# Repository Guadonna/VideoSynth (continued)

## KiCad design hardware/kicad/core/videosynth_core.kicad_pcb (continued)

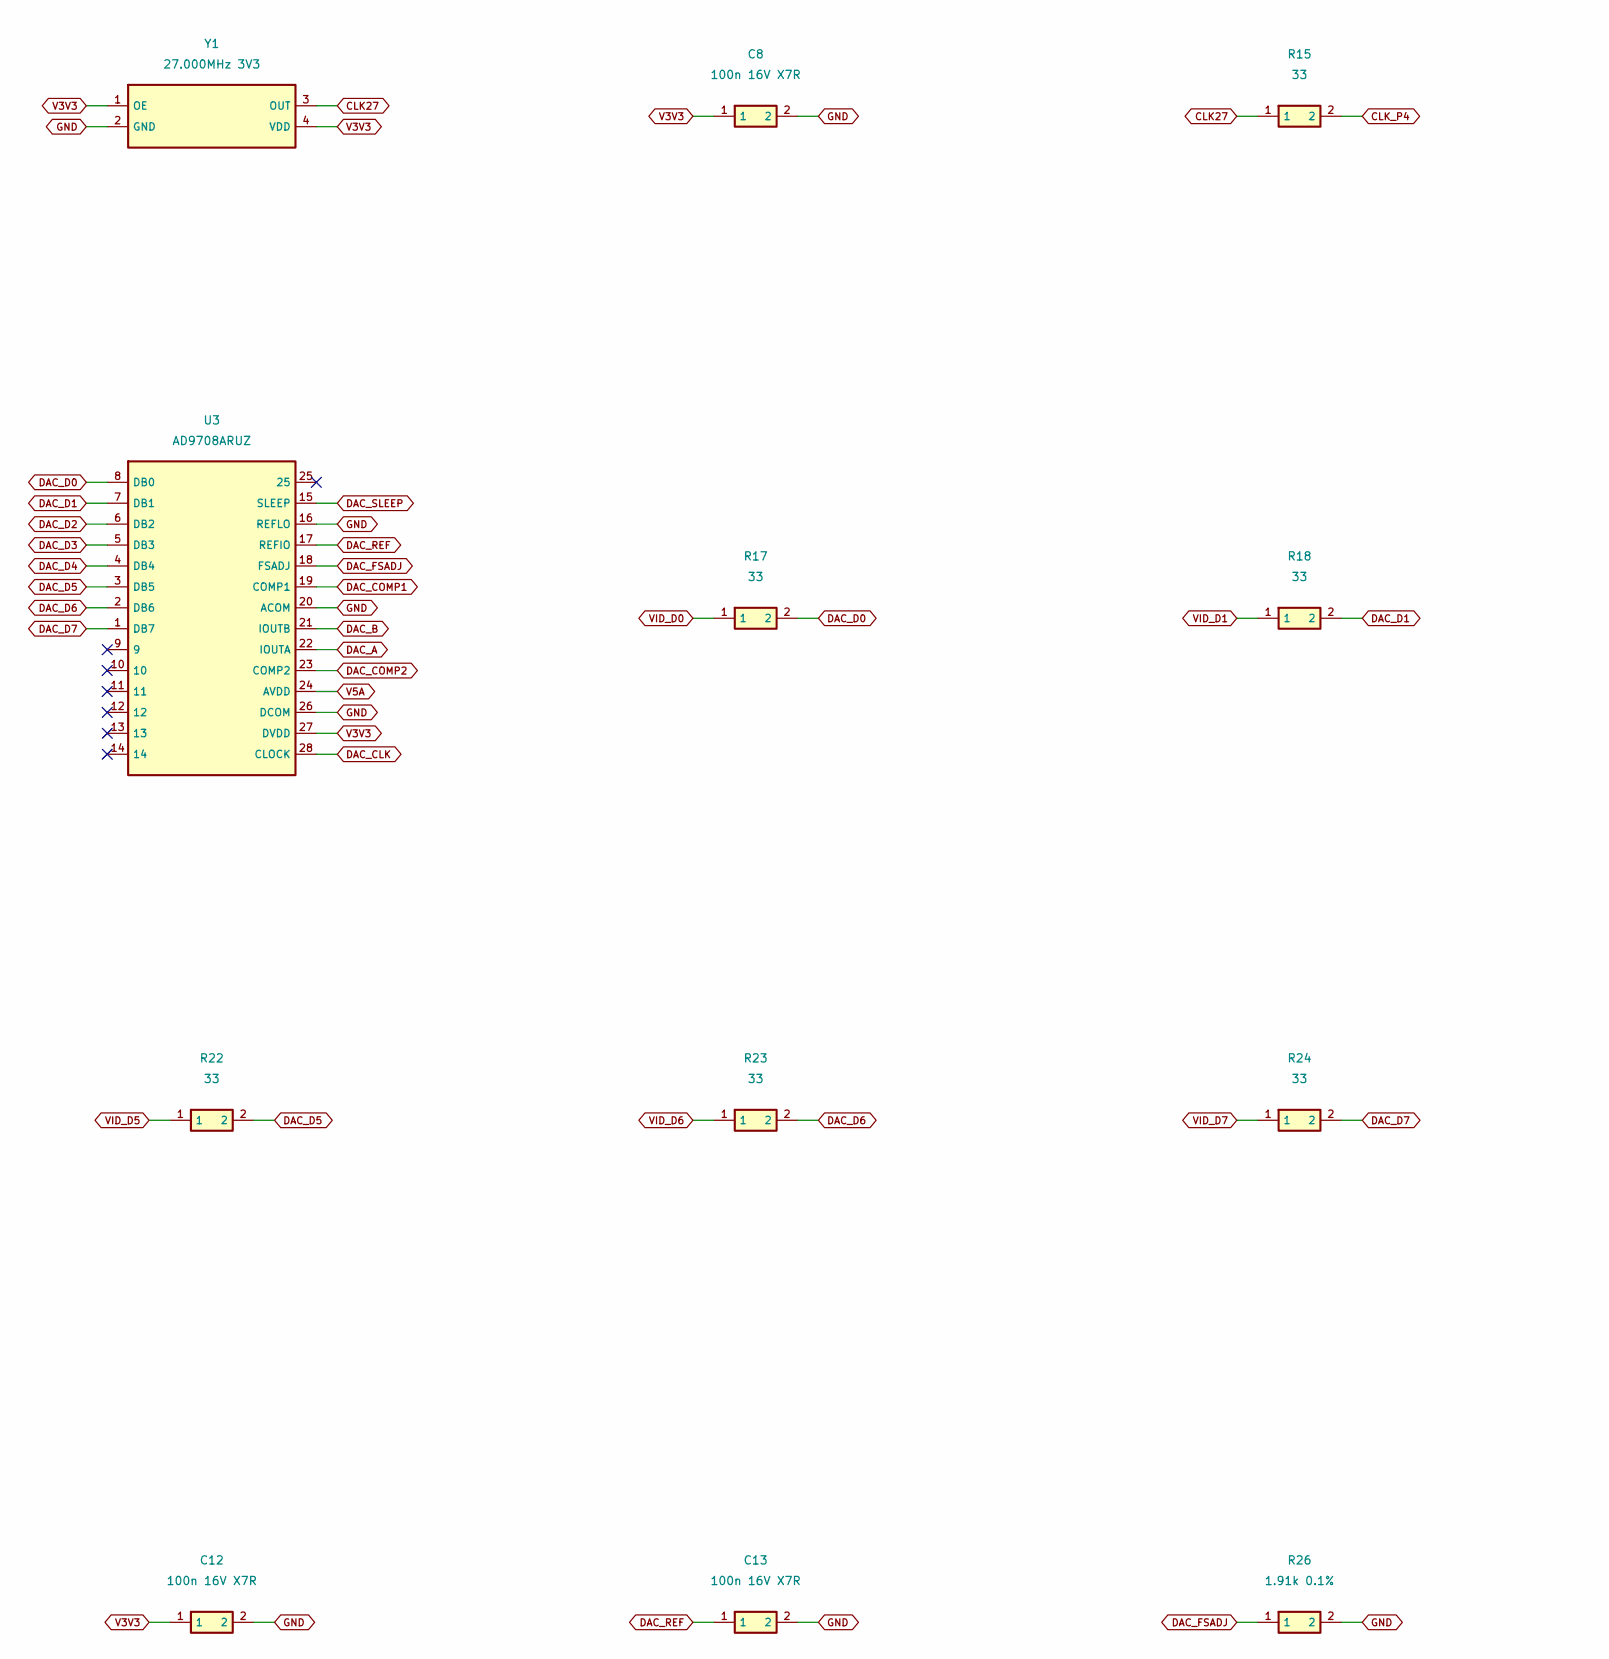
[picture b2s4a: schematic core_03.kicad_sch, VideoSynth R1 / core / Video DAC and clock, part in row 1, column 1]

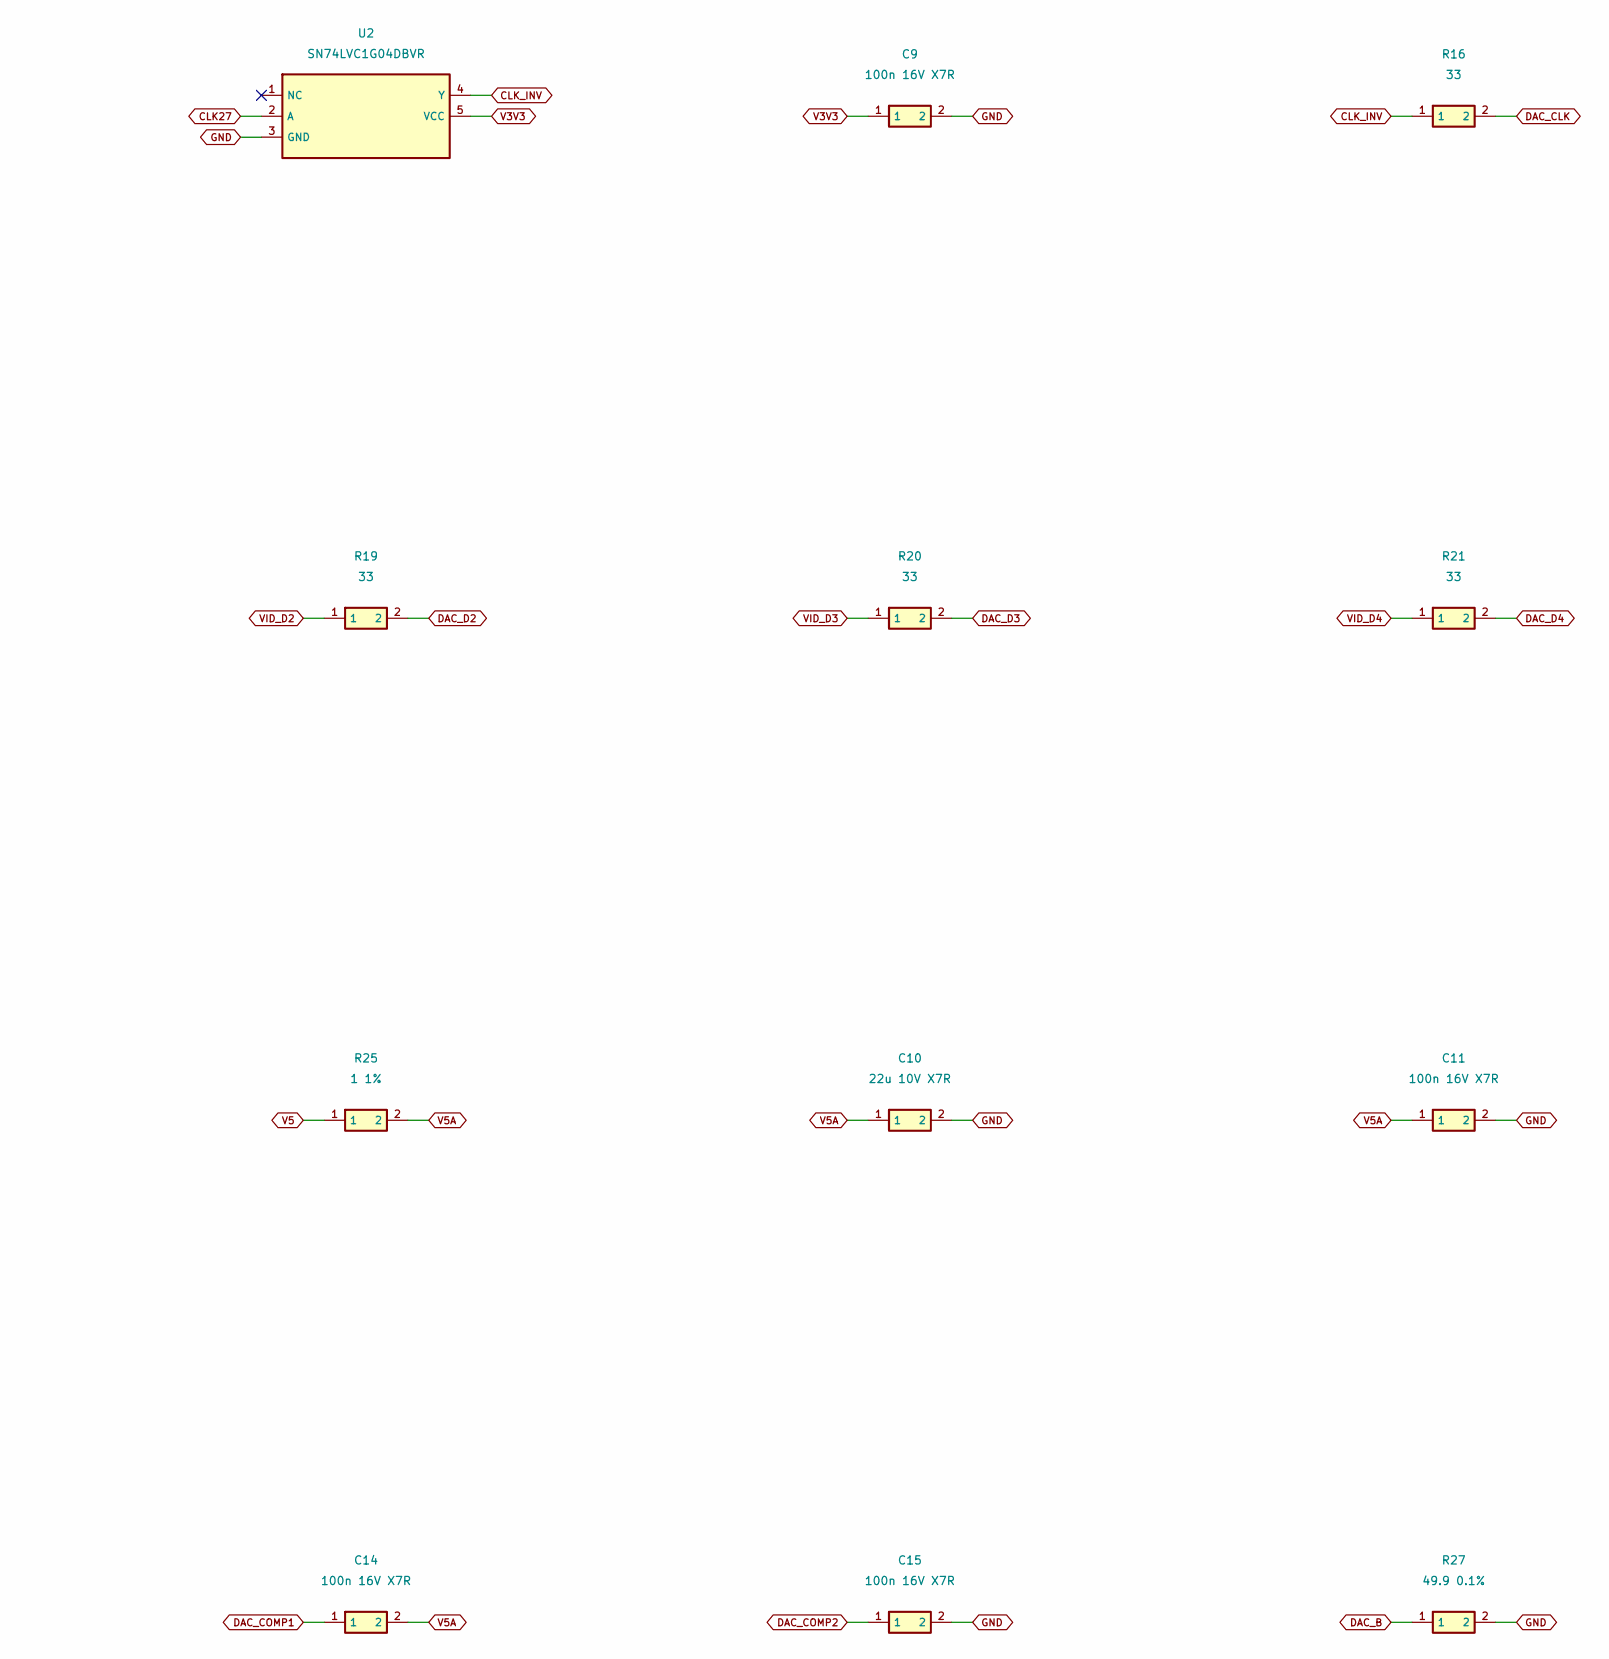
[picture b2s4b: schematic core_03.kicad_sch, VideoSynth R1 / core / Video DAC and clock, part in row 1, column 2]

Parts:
C8, C9, C11, C12, C13, C14, C15: 100n 16V X7R; C_0805_2012Metric
C10: 22u 10V X7R; C_0805_2012Metric
R15, R16, R17, R18, R19, R20, R21, R22, R23, R24: 33; R_0805_2012Metric
R25: 1 1%; R_0805_2012Metric
R26: 1.91k 0.1%; R_0805_2012Metric
R27: 49.9 0.1%; R_0805_2012Metric
U2: SN74LVC1G04DBVR; SOT-23-5
U3: AD9708ARUZ; TSSOP-28_4.4x9.7mm_P0.65mm
Y1: 27.000MHz 3V3; Oscillator_SMD_Abracon_ASE-4Pin_3.2x2.5mm

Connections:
CLK27: R15.1, U2.2 (A), Y1.3 (OUT)
CLK_INV: R16.1, U2.4 (Y)
CLK_P4: R15.2; also elsewhere on the board
DAC_A: U3.22 (IOUTA); also elsewhere on the board
DAC_B: R27.1, U3.21 (IOUTB)
DAC_CLK: R16.2, U3.28 (CLOCK)
DAC_COMP1: C14.1, U3.19 (COMP1)
DAC_COMP2: C15.1, U3.23 (COMP2)
DAC_D0: R17.2, U3.8 (DB0)
DAC_D1: R18.2, U3.7 (DB1)
DAC_D2: R19.2, U3.6 (DB2)
DAC_D3: R20.2, U3.5 (DB3)
DAC_D4: R21.2, U3.4 (DB4)
DAC_D5: R22.2, U3.3 (DB5)
DAC_D6: R23.2, U3.2 (DB6)
DAC_D7: R24.2, U3.1 (DB7)
DAC_FSADJ: R26.1, U3.18 (FSADJ)
DAC_REF: C13.1, U3.17 (REFIO)
DAC_SLEEP: U3.15 (SLEEP); also elsewhere on the board
GND: C8.2, C9.2, C10.2, C11.2, C12.2, C13.2, C15.2, R26.2, R27.2, U2.3 (GND), U3.16 (REFLO), U3.20 (ACOM), U3.26 (DCOM), Y1.2 (GND); also elsewhere on the board
V3V3: C8.1, C9.1, C12.1, U2.5 (VCC), U3.27 (DVDD), Y1.1 (OE), Y1.4 (VDD); also elsewhere on the board
V5: R25.1; also elsewhere on the board
V5A: C10.1, C11.1, C14.2, R25.2, U3.24 (AVDD); also elsewhere on the board
VID_D0: R17.1; also elsewhere on the board
VID_D1: R18.1; also elsewhere on the board
VID_D2: R19.1; also elsewhere on the board
VID_D3: R20.1; also elsewhere on the board
VID_D4: R21.1; also elsewhere on the board
VID_D5: R22.1; also elsewhere on the board
VID_D6: R23.1; also elsewhere on the board
VID_D7: R24.1; also elsewhere on the board

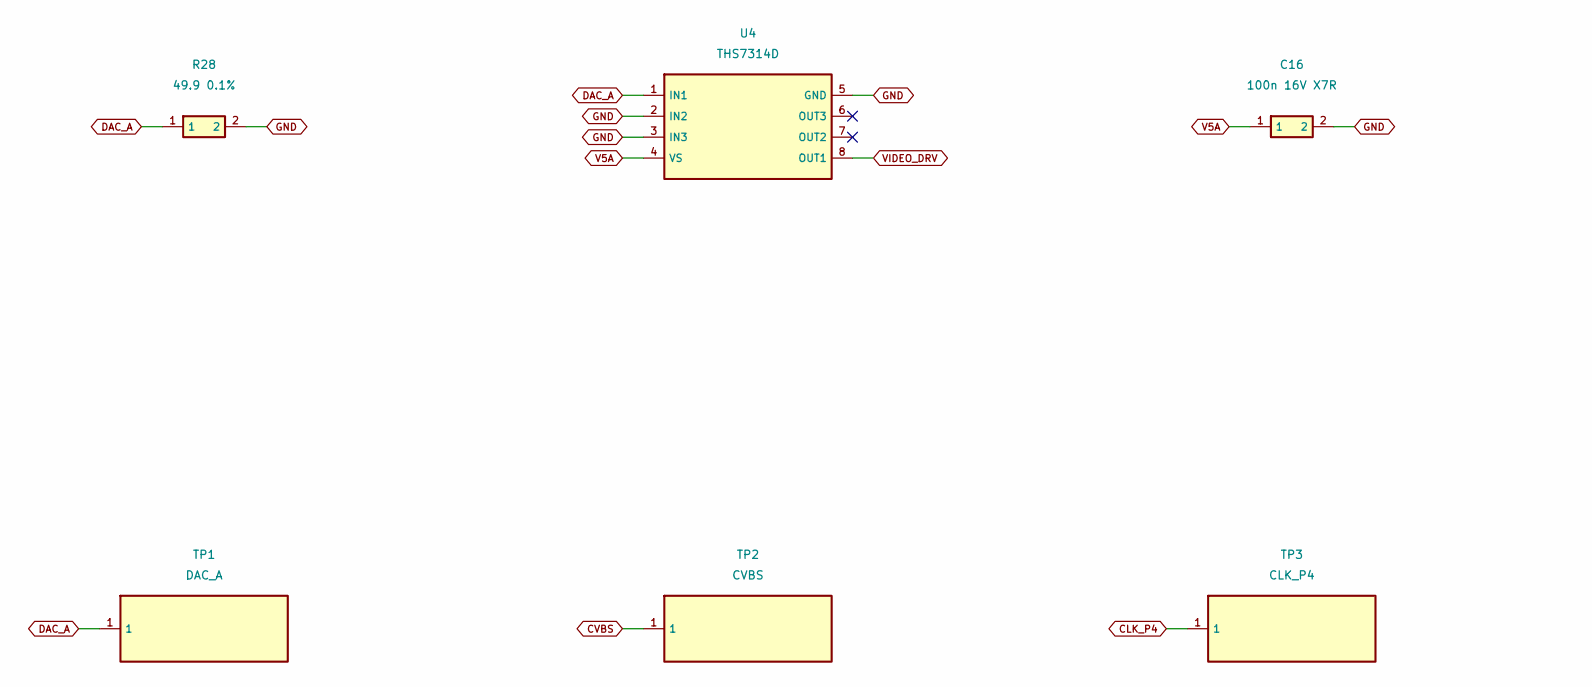
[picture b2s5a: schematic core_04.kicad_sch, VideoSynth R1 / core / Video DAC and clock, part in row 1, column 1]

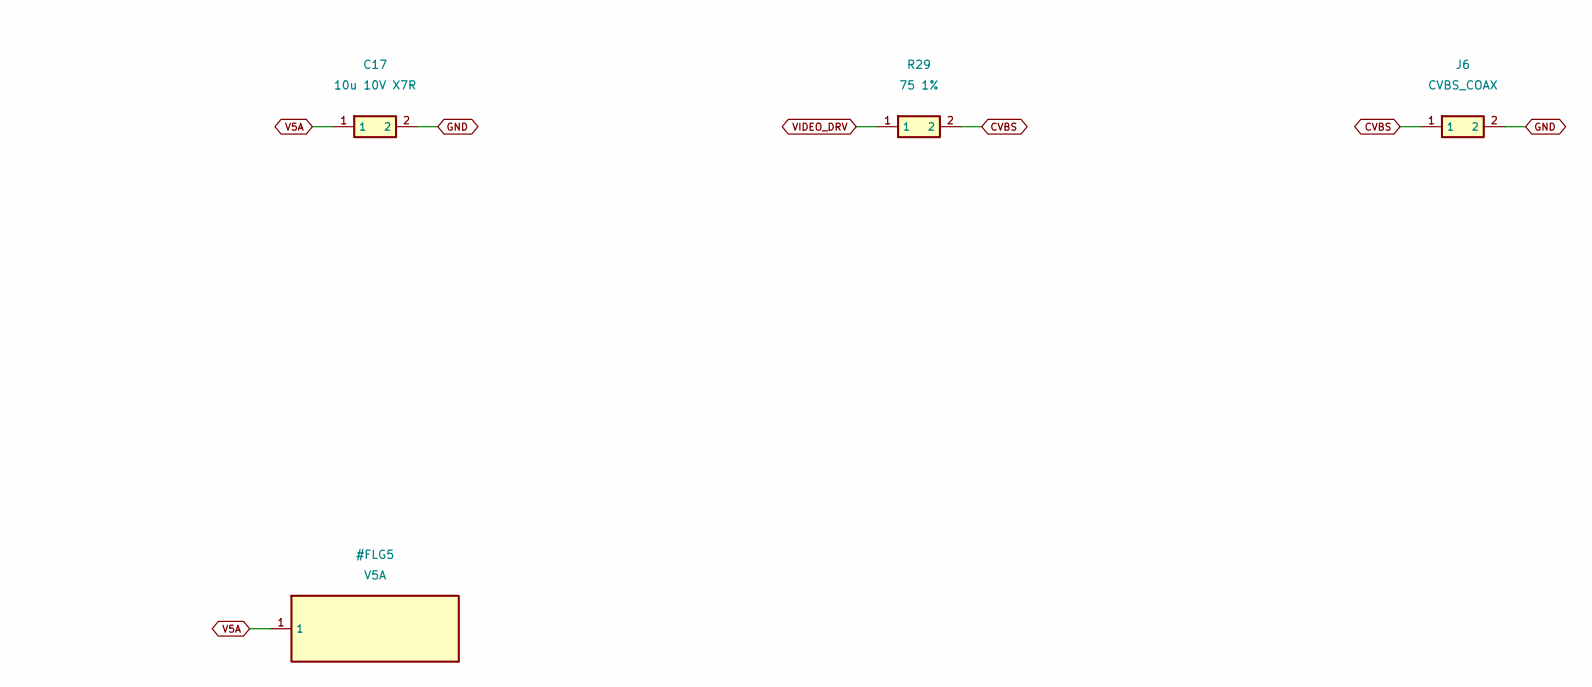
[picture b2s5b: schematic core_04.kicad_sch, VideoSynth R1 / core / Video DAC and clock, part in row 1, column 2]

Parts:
C16: 100n 16V X7R; C_0805_2012Metric
C17: 10u 10V X7R; C_0805_2012Metric
J6: CVBS_COAX; PinHeader_1x02_P2.54mm_Vertical
R28: 49.9 0.1%; R_0805_2012Metric
R29: 75 1%; R_0805_2012Metric
TP1: DAC_A; TestPoint_Pad_D1.5mm
TP2: CVBS; TestPoint_Pad_D1.5mm
TP3: CLK_P4; TestPoint_Pad_D1.5mm
U4: THS7314D; SOIC-8_3.9x4.9mm_P1.27mm

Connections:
CLK_P4: TP3.1; also elsewhere on the board
CVBS: J6.1, R29.2, TP2.1
DAC_A: R28.1, TP1.1, U4.1 (IN1); also elsewhere on the board
GND: C16.2, C17.2, J6.2, R28.2, U4.2 (IN2), U4.3 (IN3), U4.5 (GND); also elsewhere on the board
V5A: C16.1, C17.1, U4.4 (VS); also elsewhere on the board
VIDEO_DRV: R29.1, U4.8 (OUT1)

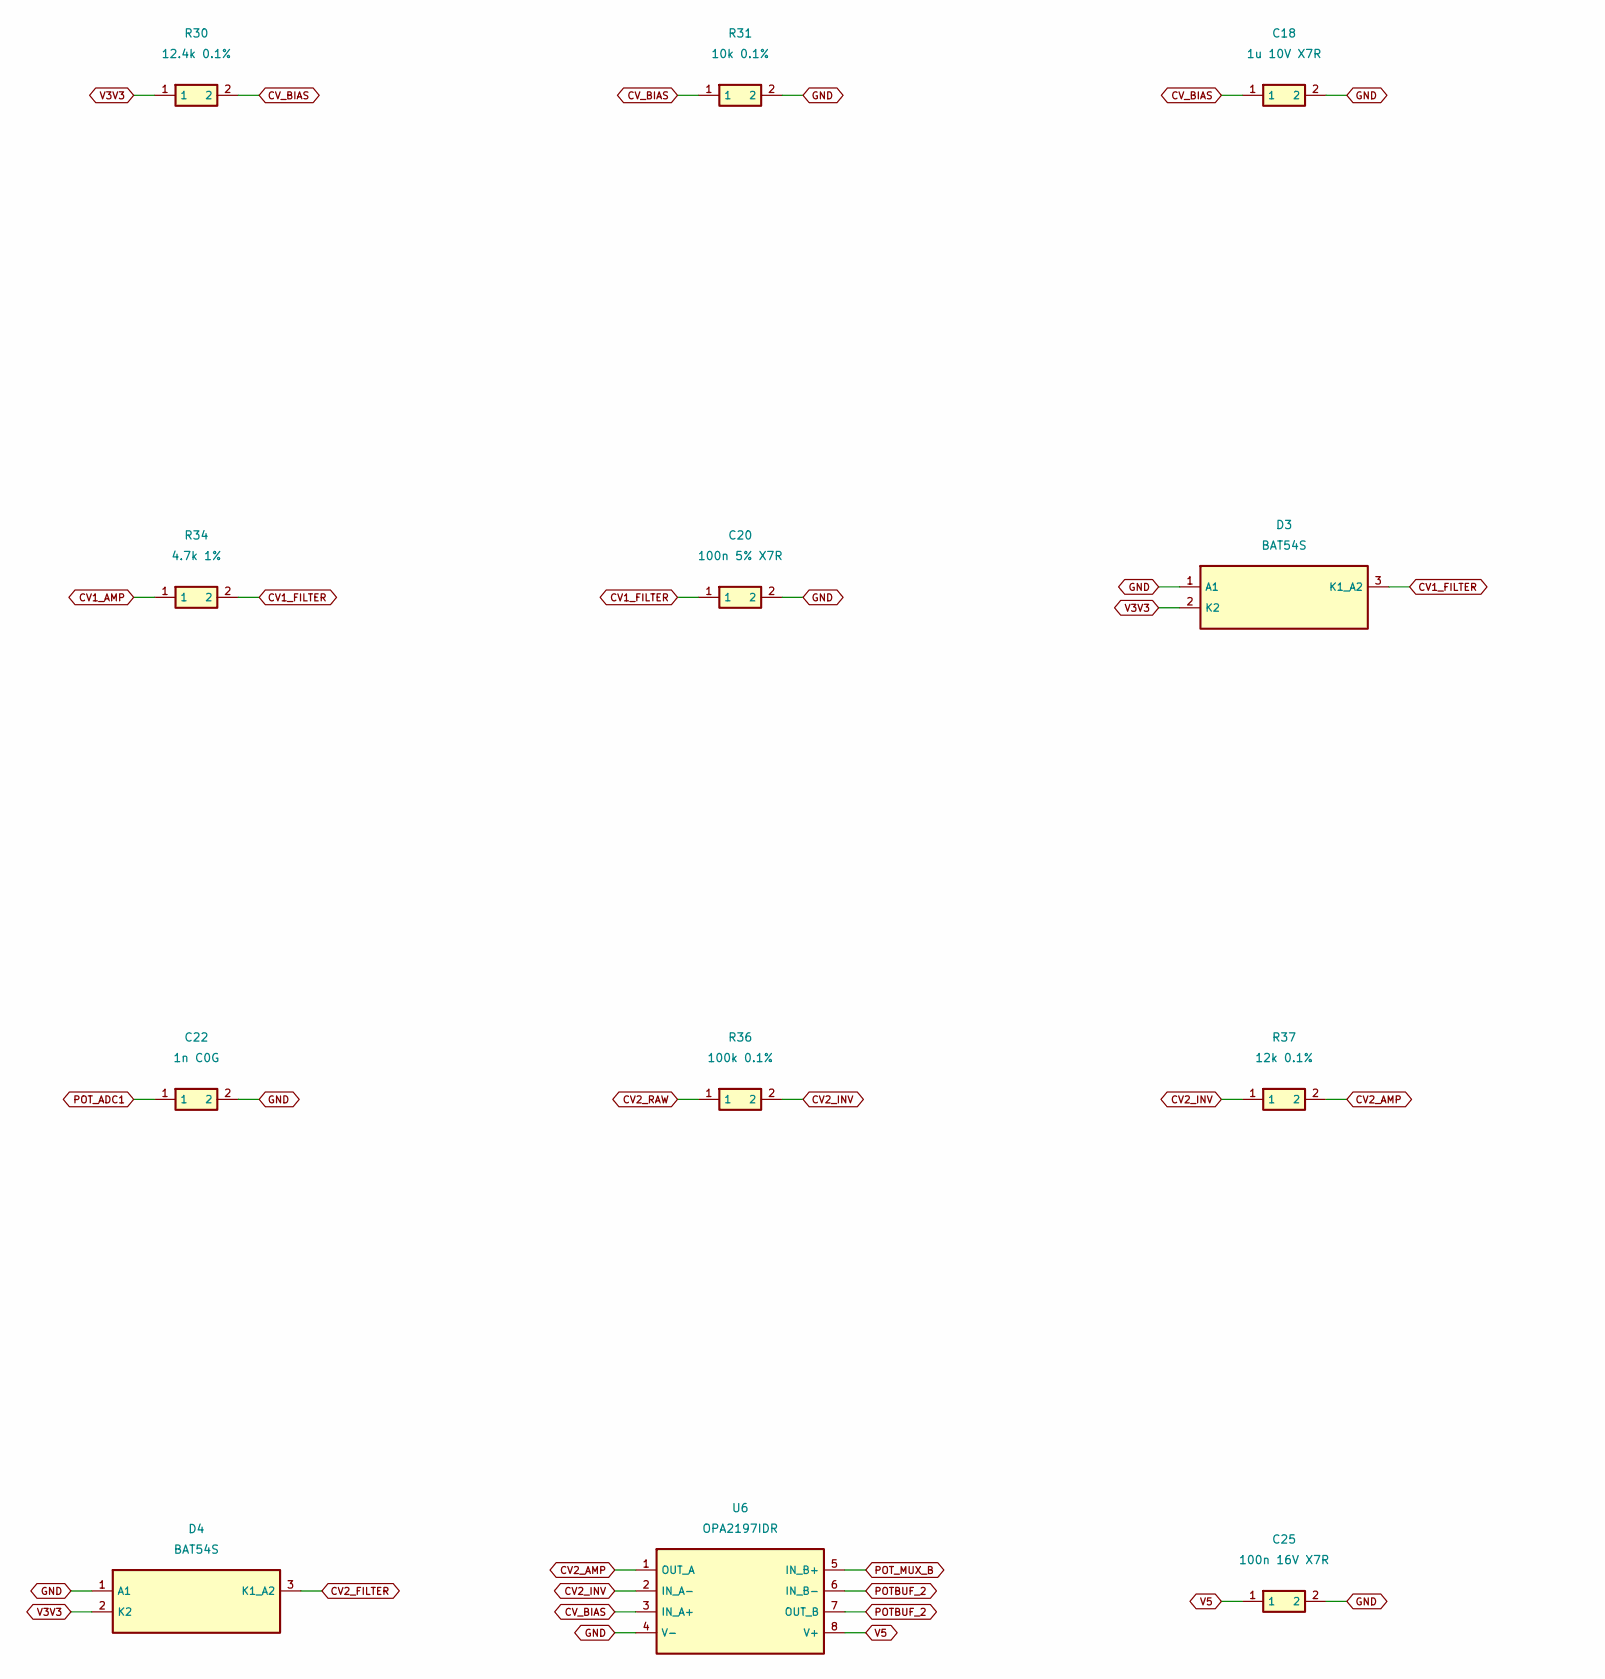
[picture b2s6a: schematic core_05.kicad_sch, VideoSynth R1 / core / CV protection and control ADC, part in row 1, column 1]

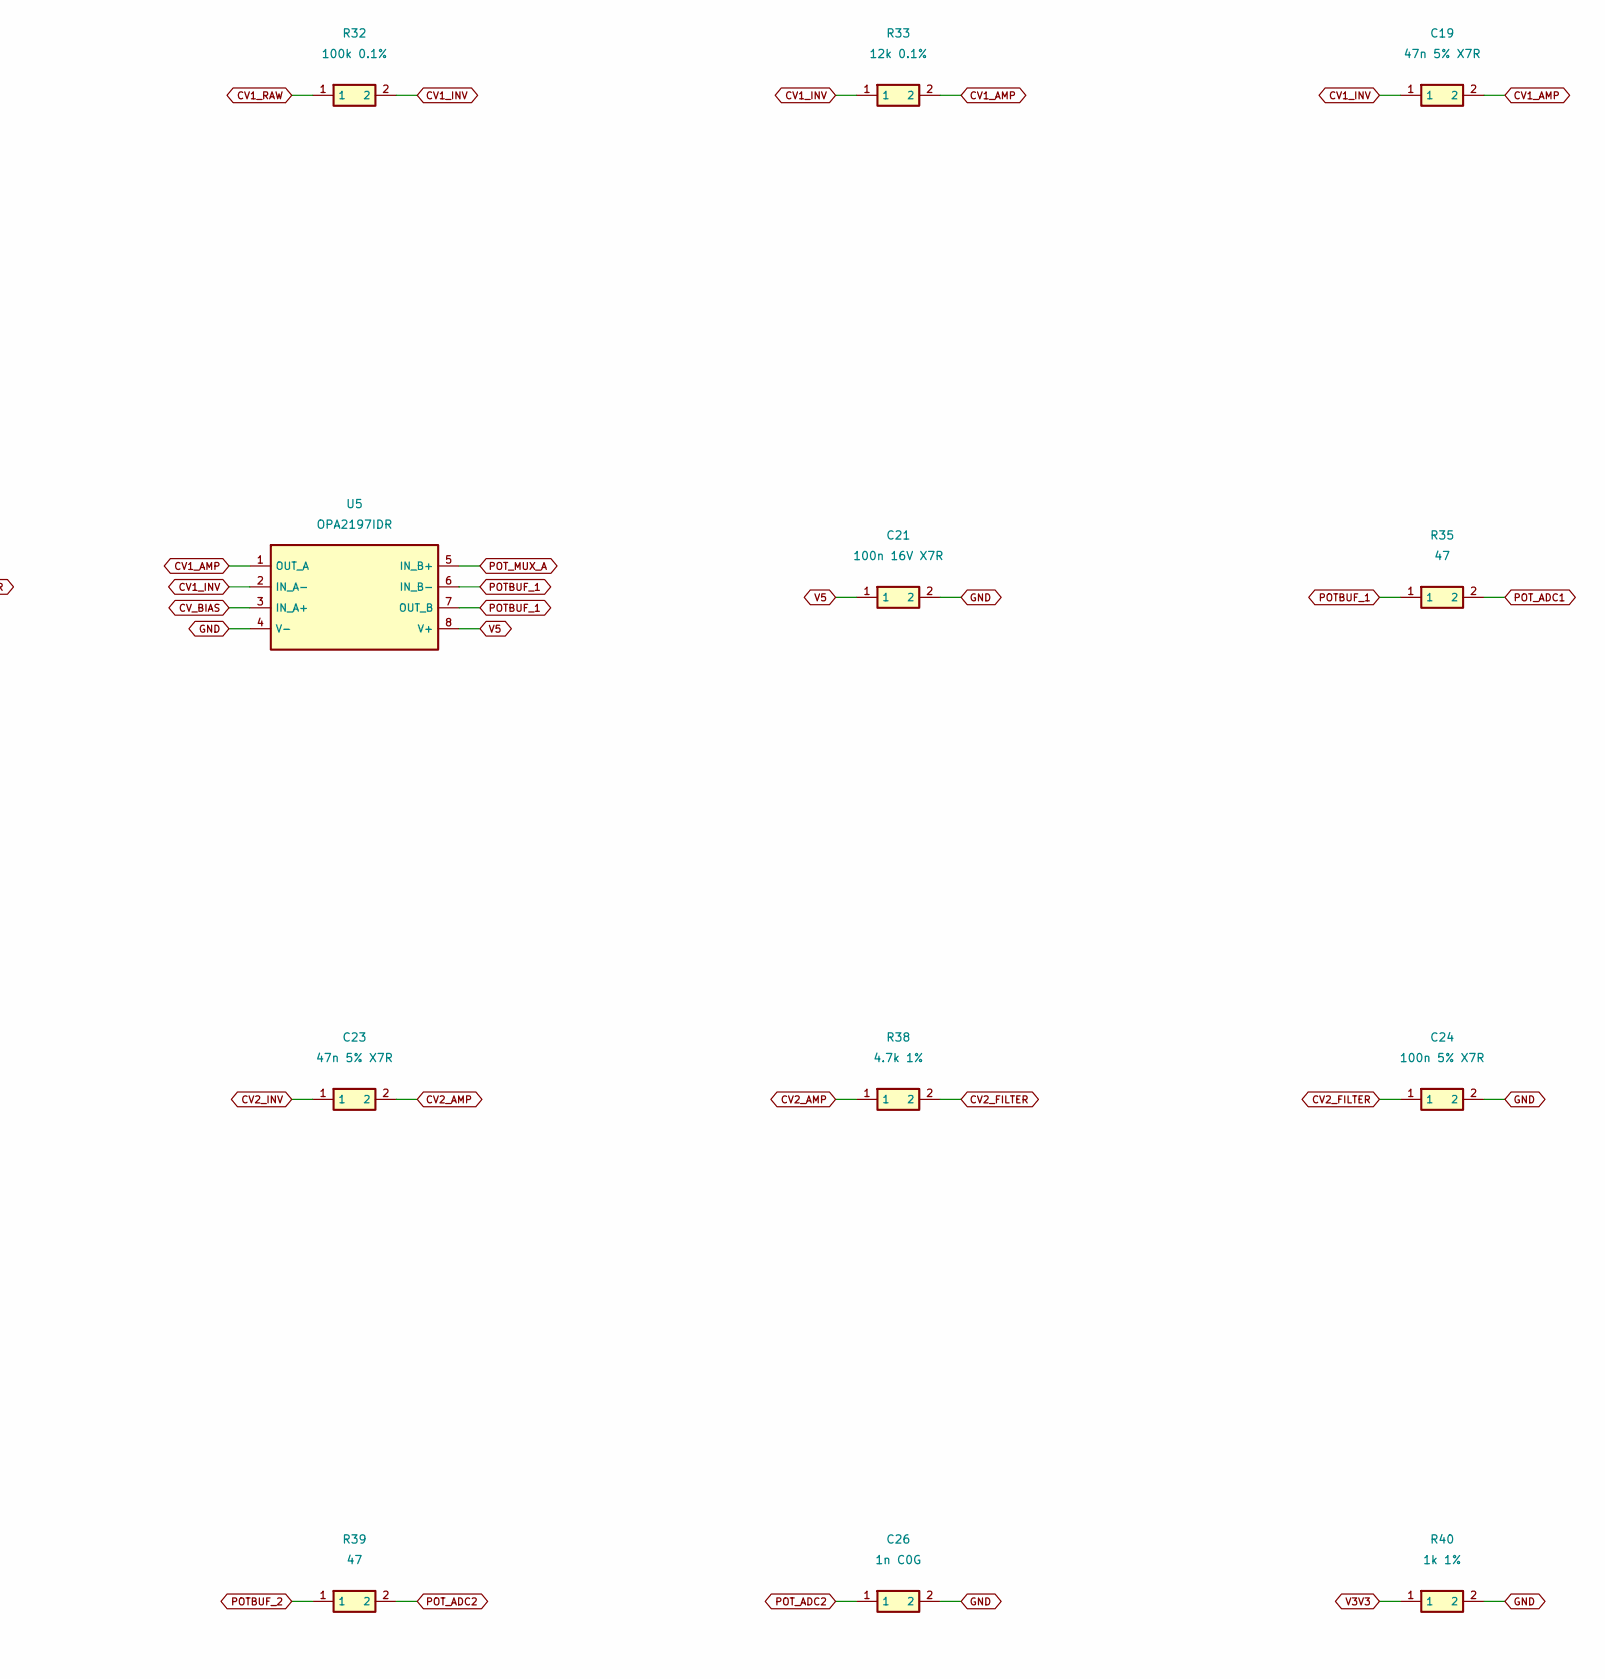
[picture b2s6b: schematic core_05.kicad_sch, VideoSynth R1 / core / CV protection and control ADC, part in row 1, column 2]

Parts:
C18: 1u 10V X7R; C_0805_2012Metric
C19, C23: 47n 5% X7R; C_0805_2012Metric
C20, C24: 100n 5% X7R; C_0805_2012Metric
C21, C25: 100n 16V X7R; C_0805_2012Metric
C22, C26: 1n C0G; C_0805_2012Metric
D3, D4: BAT54S; SOT-23
R30: 12.4k 0.1%; R_0805_2012Metric
R31: 10k 0.1%; R_0805_2012Metric
R32, R36: 100k 0.1%; R_0805_2012Metric
R33, R37: 12k 0.1%; R_0805_2012Metric
R34, R38: 4.7k 1%; R_0805_2012Metric
R35, R39: 47; R_0805_2012Metric
R40: 1k 1%; R_0805_2012Metric
U5, U6: OPA2197IDR; SOIC-8_3.9x4.9mm_P1.27mm

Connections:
CV1_AMP: C19.2, R33.2, R34.1, U5.1 (OUT_A)
CV1_FILTER: C20.1, D3.3 (K1_A2), R34.2; also elsewhere on the board
CV1_INV: C19.1, R32.2, R33.1, U5.2 (IN_A-)
CV1_RAW: R32.1; also elsewhere on the board
CV2_AMP: C23.2, R37.2, R38.1, U6.1 (OUT_A)
CV2_FILTER: C24.1, D4.3 (K1_A2), R38.2; also elsewhere on the board
CV2_INV: C23.1, R36.2, R37.1, U6.2 (IN_A-)
CV2_RAW: R36.1; also elsewhere on the board
CV_BIAS: C18.1, R30.2, R31.1, U5.3 (IN_A+), U6.3 (IN_A+)
GND: C18.2, C20.2, C21.2, C22.2, C24.2, C25.2, C26.2, D3.1 (A1), D4.1 (A1), R31.2, R40.2, U5.4 (V-), U6.4 (V-); also elsewhere on the board
POTBUF_1: R35.1, U5.6 (IN_B-), U5.7 (OUT_B)
POTBUF_2: R39.1, U6.6 (IN_B-), U6.7 (OUT_B)
POT_ADC1: C22.1, R35.2; also elsewhere on the board
POT_ADC2: C26.1, R39.2; also elsewhere on the board
POT_MUX_A: U5.5 (IN_B+); also elsewhere on the board
POT_MUX_B: U6.5 (IN_B+); also elsewhere on the board
V3V3: D3.2 (K2), D4.2 (K2), R30.1, R40.1; also elsewhere on the board
V5: C21.1, C25.1, U5.8 (V+), U6.8 (V+); also elsewhere on the board

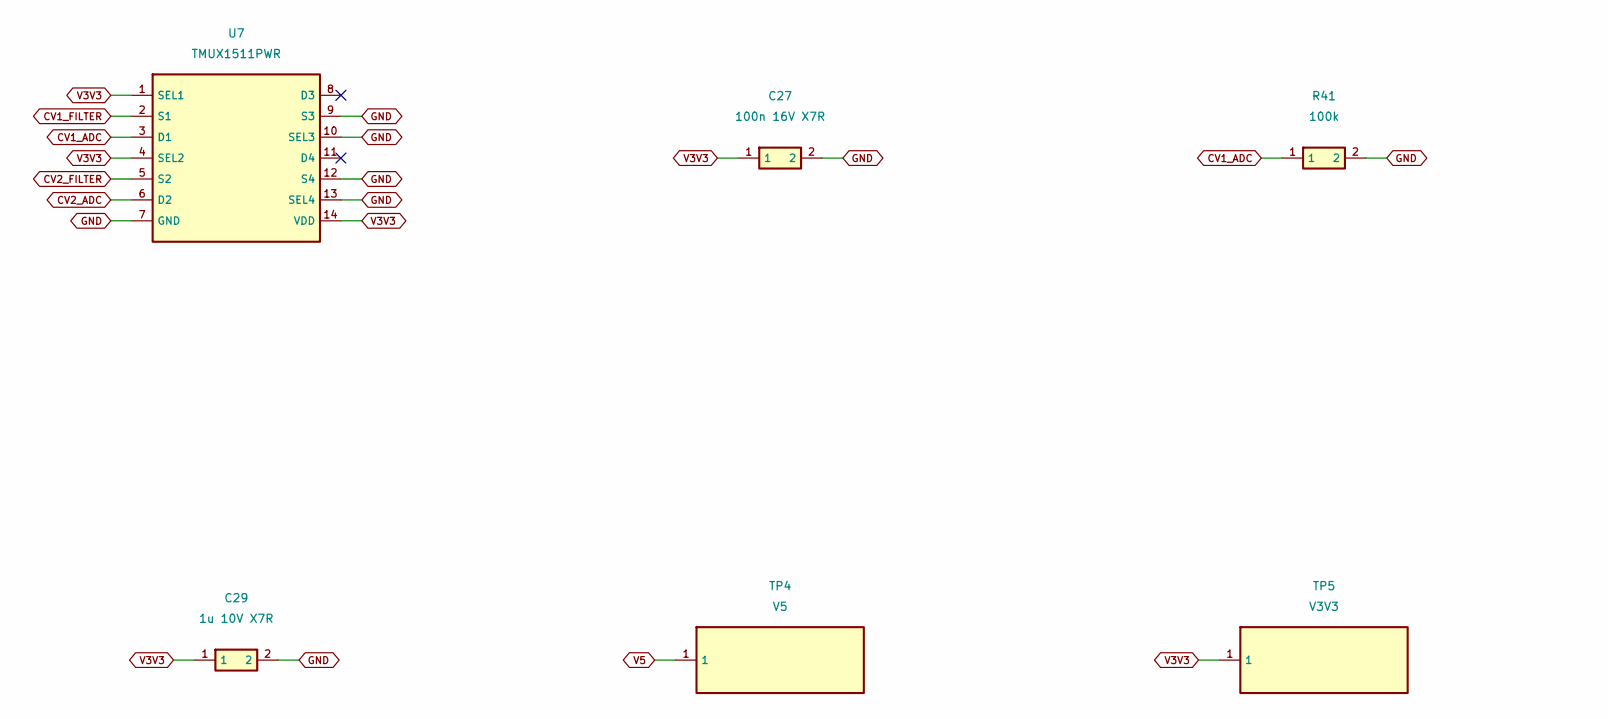
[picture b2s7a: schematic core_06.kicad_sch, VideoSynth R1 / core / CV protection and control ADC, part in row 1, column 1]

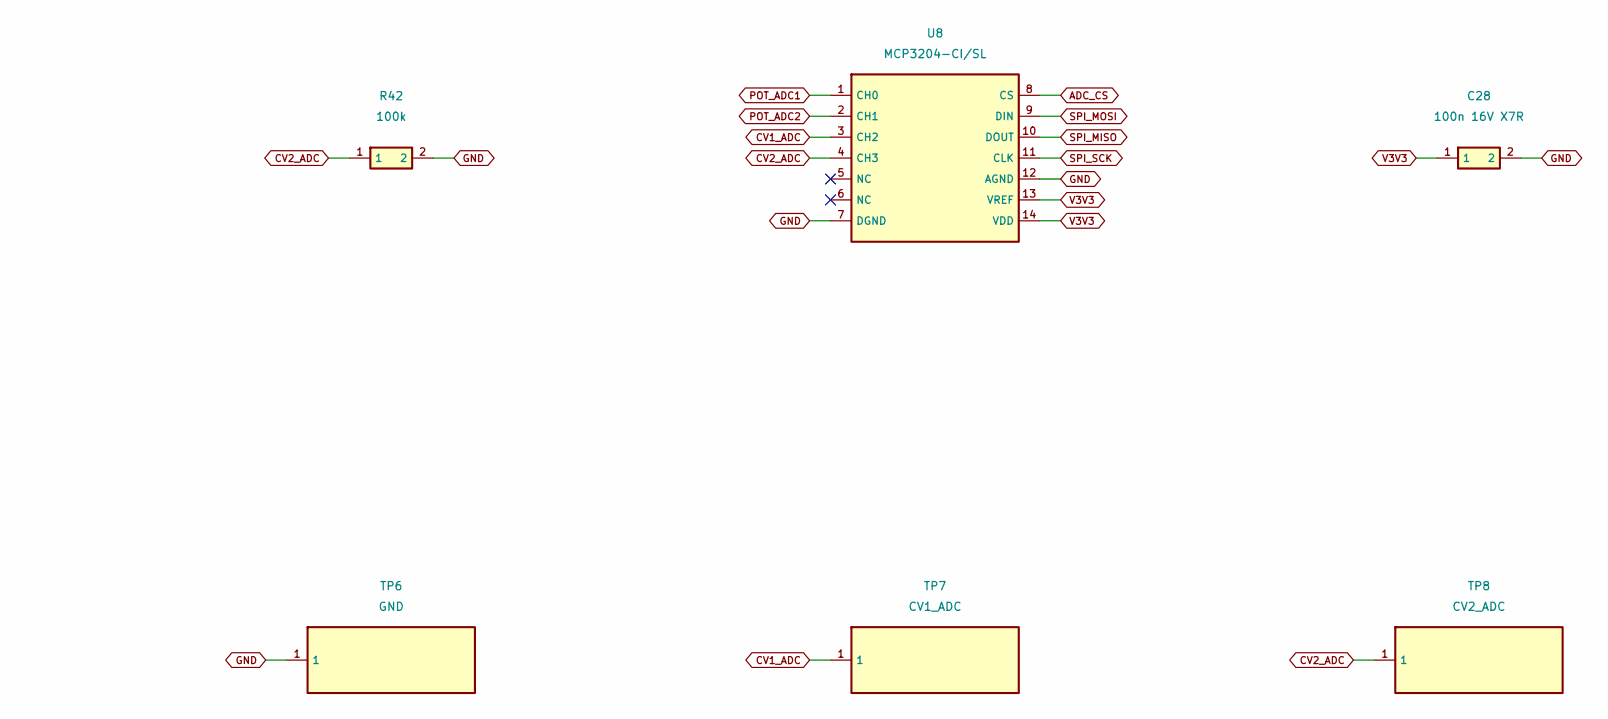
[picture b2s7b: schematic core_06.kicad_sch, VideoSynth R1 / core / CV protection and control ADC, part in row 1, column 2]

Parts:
C27, C28: 100n 16V X7R; C_0805_2012Metric
C29: 1u 10V X7R; C_0805_2012Metric
R41, R42: 100k; R_0805_2012Metric
TP4: V5; TestPoint_Pad_D1.5mm
TP5: V3V3; TestPoint_Pad_D1.5mm
TP6: GND; TestPoint_Pad_D1.5mm
TP7: CV1_ADC; TestPoint_Pad_D1.5mm
TP8: CV2_ADC; TestPoint_Pad_D1.5mm
U7: TMUX1511PWR; TSSOP-14_4.4x5mm_P0.65mm
U8: MCP3204-CI/SL; SOIC-14_3.9x8.7mm_P1.27mm

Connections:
ADC_CS: U8.8 (CS); also elsewhere on the board
CV1_ADC: R41.1, TP7.1, U7.3 (D1), U8.3 (CH2)
CV1_FILTER: U7.2 (S1); also elsewhere on the board
CV2_ADC: R42.1, TP8.1, U7.6 (D2), U8.4 (CH3)
CV2_FILTER: U7.5 (S2); also elsewhere on the board
GND: C27.2, C28.2, C29.2, R41.2, R42.2, TP6.1, U7.7 (GND), U7.9 (S3), U7.10 (SEL3), U7.12 (S4), U7.13 (SEL4), U8.7 (DGND), U8.12 (AGND); also elsewhere on the board
POT_ADC1: U8.1 (CH0); also elsewhere on the board
POT_ADC2: U8.2 (CH1); also elsewhere on the board
SPI_MISO: U8.10 (DOUT); also elsewhere on the board
SPI_MOSI: U8.9 (DIN); also elsewhere on the board
SPI_SCK: U8.11 (CLK); also elsewhere on the board
V3V3: C27.1, C28.1, C29.1, TP5.1, U7.1 (SEL1), U7.4 (SEL2), U7.14 (VDD), U8.13 (VREF), U8.14 (VDD); also elsewhere on the board
V5: TP4.1; also elsewhere on the board

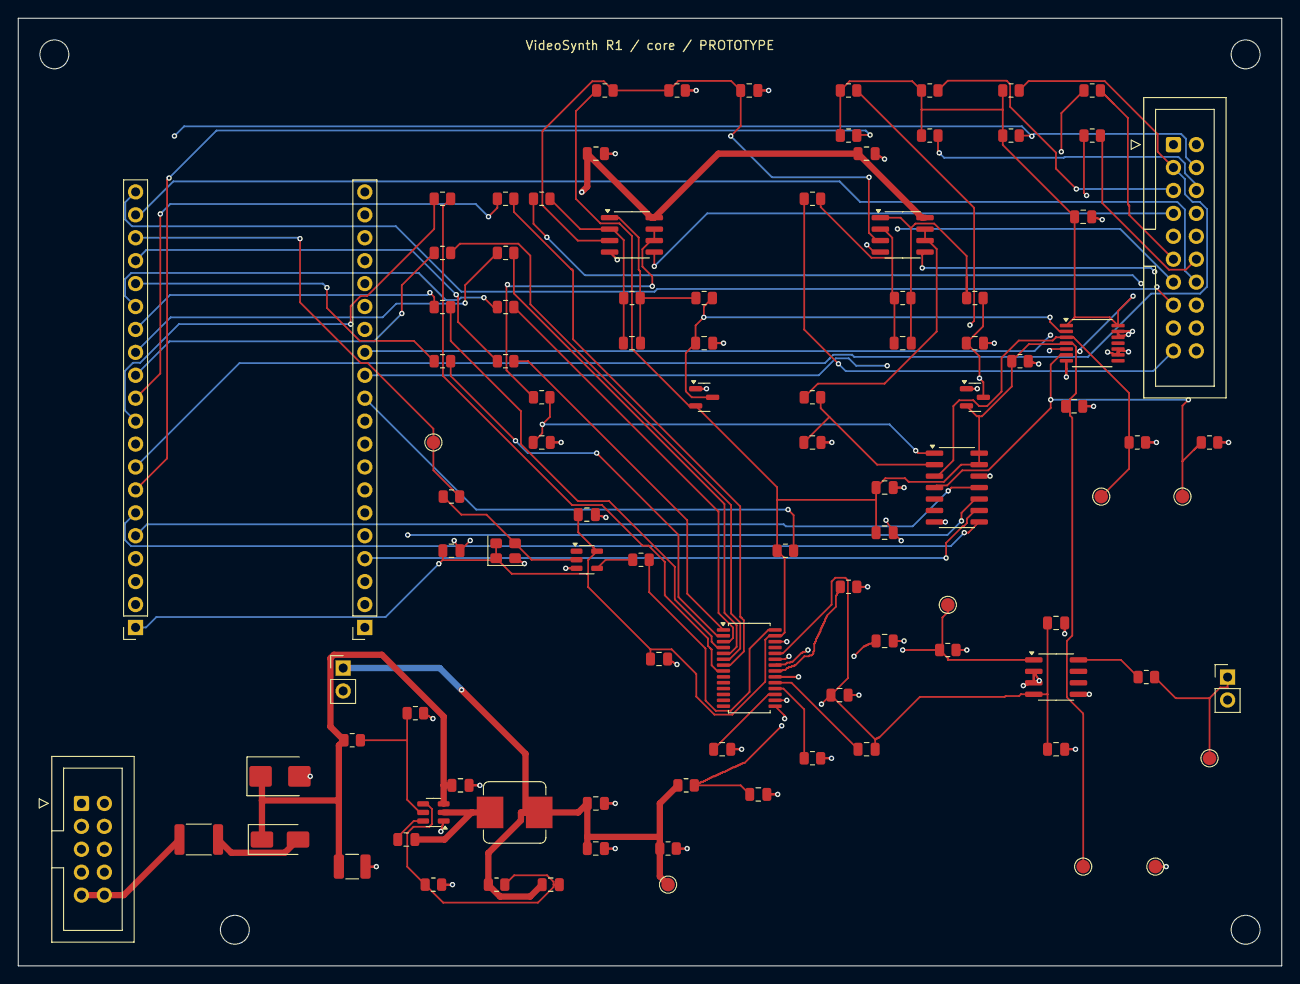
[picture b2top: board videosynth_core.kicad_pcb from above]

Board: 4 copper layers, 140.0 x 105.0 mm, 104 parts (0 on the bottom side), 70 nets.

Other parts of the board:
H1, H2, H3, H4: MountingHole_3.2mm_M3

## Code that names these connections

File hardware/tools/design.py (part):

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def chip(value,fp,pins,xy,names,types=None,**kw):return add('U',value,fp,pins,xy,names=names,types=types or {},**kw)
# CORE, 140 x 105 mm, 4 copper layers: F / GND / In2 signal / B.
# Eurorack standard: pins 1/2 -12, 3..8 GND, 9/10 +12. Negative rail intentionally unused.
add('J','EURORACK_10','Connector_IDC:IDC-Header_2x05_P2.54mm_Vertical',{1:None,2:None,**{i:'GND' for i in range(3,9)},9:'EUR_12',10:'EUR_12'},(7,87),note='Stripe = pins 1/2, -12 V NC. Use keyed 10-pin ribbon.')
add('F','750mA HOLD 33V','Fuse:Fuse_1812_4532Metric',{1:'EUR_12',2:'FUSED_12'},(20,91),mpn='Bourns MF-MSMF075-2')
add('D','SS34','Diode_SMD:D_SMA',{1:'VIN',2:'FUSED_12'},(29,91),names={1:'K',2:'A'},note='Series reverse polarity diode, 40 V')
add('D','SMBJ15A','Diode_SMD:D_SMB',{1:'VIN',2:'GND'},(29,84),names={1:'K',2:'A'},note='TVS after fuse/series diode; surge qualification required')
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add('J','OLIMEX_EXT1','Connector_PinSocket_2.54mm:PinSocket_1x20_P2.54mm_Vertical',ext1,(13,67.5),angle=180,note='Olimex ESP32-P4-DevKit Rev.D1 EXT1, top-view exact pin correspondence')
ext2={1:None,2:'GND',3:'SPI_MISO',4:'SPI_MOSI',5:None,6:None,7:None,8:None,9:None,10:None,11:'DAC_SLEEP',12:'UI_IRQ2',13:'UI_IRQ1',14:None,15:'GND',16:None,17:None,18:'GND',19:None,20:None}
add('J','OLIMEX_EXT2','Connector_PinSocket_2.54mm:PinSocket_1x20_P2.54mm_Vertical',ext2,(38.4,67.5),angle=180,note='EXT2 pin1 +5V intentionally NC. Supply through POE_PWR1 only. REMOVE module FET2 to disconnect USB power.')
panelpins={1:'V3V3',2:'GND',3:'I2C_SDA',4:'I2C_SCL',5:'UI_IRQ1',6:'UI_IRQ2',7:'POT_MUX_A',8:'GND',9:'POT_MUX_B',10:'GND',11:'TFT_SCK',12:'TFT_MOSI',13:'TFT_CS',14:'TFT_DC',15:'TFT_RST',16:'GND',17:'CV1_RAW',18:'GND',19:'CV2_RAW',20:'GND'}
add('J','PANEL_20',IDC,panelpins,(128,14),note='Straight-through keyed cable <=50 mm, same pin numbers on panel.')
R('33','SPI_SCK','TFT_SCK',(119,8));R('33','SPI_MOSI','TFT_MOSI',(119,13))
R('2.2k','V3V3','I2C_SDA',(110,8));R('2.2k','V3V3','I2C_SCL',(110,13))
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R('10k','V3V3','ADC_CS',(92,8));R('10k','V3V3','TFT_CS',(92,13));R('100k','V3V3','DAC_SLEEP',(85,59))
C('10u 10V X7R','V3V3','GND',(118,22))
GROUP='Video DAC and clock'
add('Y','27.000MHz 3V3','Oscillator:Oscillator_SMD_Abracon_ASE-4Pin_3.2x2.5mm',{1:'V3V3',2:'GND',3:'CLK27',4:'V3V3'},(54,59),mpn='ASE-27.000MHZ-LC-T',names={1:'OE',2:'GND',3:'OUT',4:'VDD'},types={1:'input',2:'power_in',3:'output',4:'power_in'})
dec('V3V3',(48,59));R('33','CLK27','CLK_P4',(48,53))
chip('SN74LVC1G04DBVR','Package_TO_SOT_SMD:SOT-23-5',{1:None,2:'CLK27',3:'GND',4:'CLK_INV',5:'V3V3'},(63,60),{1:'NC',2:'A',3:'GND',4:'Y',5:'VCC'},{2:'input',3:'power_in',4:'output',5:'power_in'})
dec('V3V3',(63,55));R('33','CLK_INV','DAC_CLK',(69,60))
# PARLIO must launch data on CLK27 rising edge, DAC latches on inverted edge.
vidpins={**{8-i:f'DAC_D{i}' for i in range(8)},**{i:None for i in list(range(9,15))+[25]},15:'DAC_SLEEP',16:'GND',17:'DAC_REF',18:'DAC_FSADJ',19:'DAC_COMP1',20:'GND',21:'DAC_B',22:'DAC_A',23:'DAC_COMP2',24:'V5A',26:'GND',27:'V3V3',28:'DAC_CLK'}
vidnames={**{8-i:f'DB{i}' for i in range(8)},15:'SLEEP',16:'REFLO',17:'REFIO',18:'FSADJ',19:'COMP1',20:'ACOM',21:'IOUTB',22:'IOUTA',23:'COMP2',24:'AVDD',26:'DCOM',27:'DVDD',28:'CLOCK'}
vidtypes={**{i:'input' for i in range(1,9)},15:'input',20:'power_in',21:'output',22:'output',24:'power_in',26:'power_in',27:'power_in',28:'input'}
chip('AD9708ARUZ','Package_SO:TSSOP-28_4.4x9.7mm_P0.65mm',vidpins,(81,72),vidnames,vidtypes)
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C('10u 10V X7R','V3V3','GND',(185,8),side='B')
# Expanders have no buttons on the matrix; they scan actual UI controls and select mux channels.
for ui,xy in [(1,(156,24)),(2,(181,24))]:
 pins={**{i:None for i in range(1,29)},9:'V3V3',10:'GND',12:'I2C_SCL',13:'I2C_SDA',15:'GND' if ui==1 else 'V3V3',16:'GND',17:'GND',18:'UI_RESET',20:f'UI_IRQ{ui}'}
 names={9:'VDD',10:'VSS',11:'NC',12:'SCL',13:'SDA',14:'NC',15:'A0',16:'A1',17:'A2',18:'RESET',19:'INTB',20:'INTA'}
 for i in range(8):names[i+1]=f'GPB{i}';names[i+21]=f'GPA{i}'
 if ui==1:
  for i in range(8):pins[21+i]=f'BUTTON{i}'
  for i in range(6):pins[1+i]=f'LED{i}'
  pins[7]='BL_GATE'
 else:
  for i in range(4):pins[21+i]=f'MUX_S{i}'
  for i,n in enumerate(['ENC_X_A','ENC_X_B','ENC_Y_A','ENC_Y_B']):pins[25+i]=n
 typ={9:'power_in',10:'power_in',12:'input',13:'bidirectional',15:'input',16:'input',17:'input',18:'input',19:'open_collector',20:'open_collector',**{i:'bidirectional' for i in list(range(1,9))+list(range(21,29))}}
 chip('MCP23017-E/SO','Package_SO:SOIC-28W_7.5x17.9mm_P1.27mm',pins,xy,names,typ,side='B',note='I2C address '+('0x20' if ui==1 else '0x21')+'; IRQ open-drain active-low; configure output latches before direction.')
 decp=dec('V3V3',(xy[0]-10,xy[1]));decp['side']='B'
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for mux,xy in [(0,(45,46)),(1,(111,46))]:
 # CD74HC4067M channels are not sequential package pins.
 chpins=[9,8,7,6,5,4,3,2,23,22,21,20,19,18,17,16]
 pins={1:'POT_MUX_'+('A' if mux==0 else 'B'),10:'MUX_S0',11:'MUX_S1',12:'GND',13:'MUX_S3',14:'MUX_S2',15:'GND',24:'V3V3'}
 for ch,pin in enumerate(chpins):pins[pin]=f'POT{mux*12+ch:02}' if ch<12 else 'GND'
 names={1:'COM',10:'S0',11:'S1',12:'GND',13:'S3',14:'S2',15:'EN_N',24:'VCC',**{p:f'CH{i}' for i,p in enumerate(chpins)}}
 chip('CD74HC4067M96','Package_SO:SOIC-24W_7.5x15.4mm_P1.27mm',pins,xy,names,{10:'input',11:'input',12:'power_in',13:'input',14:'input',15:'input',24:'power_in'},side='B',angle=90)
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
